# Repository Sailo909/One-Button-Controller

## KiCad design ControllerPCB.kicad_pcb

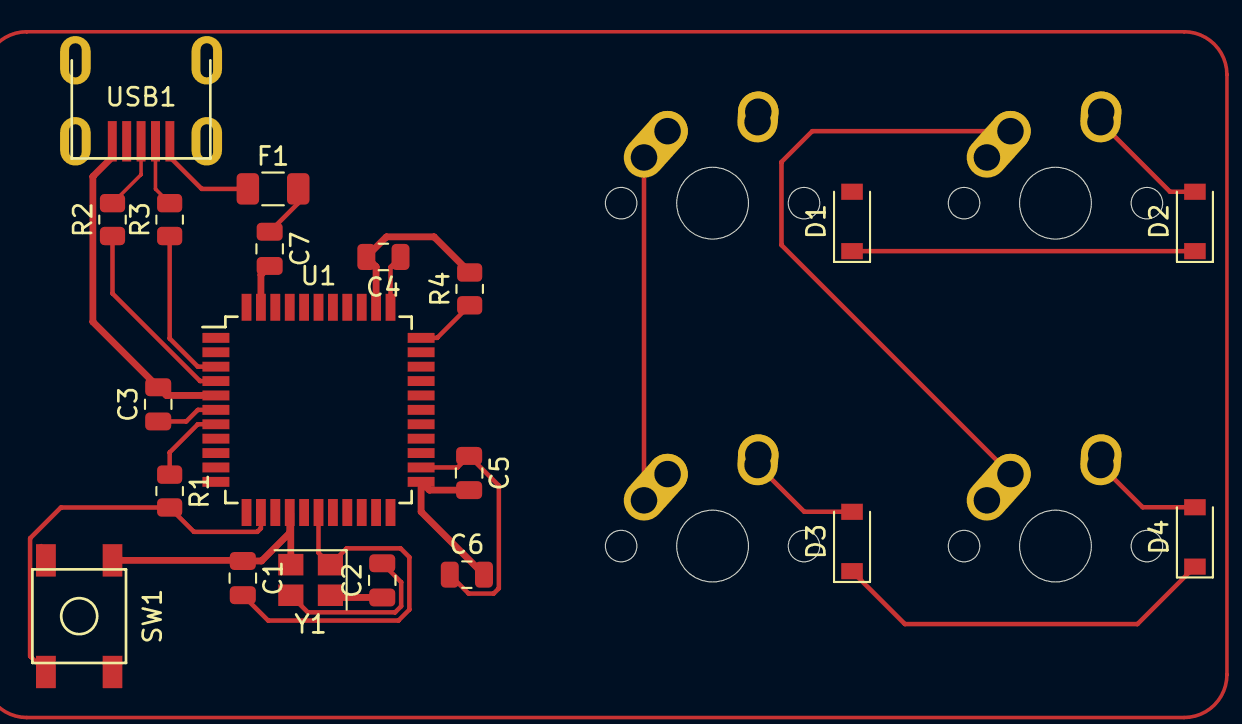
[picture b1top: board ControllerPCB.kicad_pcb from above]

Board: 2 copper layers, 24 parts (0 on the bottom side), 20 nets.

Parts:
C1, C2: 22pF; C_0805_2012Metric
C3: 1uF; C_0805_2012Metric
C4, C5, C6: 0.1uF; C_0805_2012Metric
C7: 10uF; C_0805_2012Metric
D1, D2, D3, D4: SOD-123; D_SOD-123
F1: 500mA; Fuse_1206_3216Metric
MX1, MX2, MX3, MX4: MX-NoLED; MX-1U-NoLED
R1, R4: 10k; R_0805_2012Metric
R2, R3: 22; R_0805_2012Metric
SW1: SW_Push; SKQG-1155865
U1: ATmega32U4-A; TQFP-44_10x10mm_P0.8mm
USB1: Molex-0548190589
Y1: 16MHz; Crystal_SMD_3225-4Pin_3.2x2.5mm

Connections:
+5V: C4.1, C5.1, C6.1, C7.1, F1.2, R1.1, U1.2 (UVCC), U1.7 (VBUS), U1.14 (VCC), U1.24 (AVCC), U1.34 (VCC), U1.44 (AVCC)
/D+: R2.2, USB1.3 (D+)
/D-: R3.2, USB1.4 (D-)
/ROW-0: D1.1 (K), D2.1 (K)
/ROW-1: D3.1 (K), D4.1 (K)
GND: C1.1, C2.1, C3.2, C4.2, C5.2, C6.2, C7.2, R4.2, SW1.1, U1.5 (UGND), U1.15 (GND), U1.23 (GND), U1.35 (GND), U1.43 (GND), USB1.1 (GND), Y1.2, Y1.4
unnamed: C1.2, U1.17 (XTAL1), Y1.1
unnamed: C2.2, U1.16 (XTAL2), Y1.3
unnamed: C3.1, U1.6 (UCAP)
unnamed: D1.2 (A), MX1.2 (ROW)
unnamed: D2.2 (A), MX2.2 (ROW)
unnamed: D3.2 (A), MX3.2 (ROW)
unnamed: D4.2 (A), MX4.2 (ROW)
unnamed: MX1.1 (COL), MX3.1 (COL)
unnamed: MX2.1 (COL), MX4.1 (COL)
unnamed: R1.2, SW1.2, U1.13 (~RESET)
unnamed: R2.1, U1.4 (D+)
unnamed: R3.1, U1.3 (D-)
unnamed: R4.1, U1.33 (~HWB/PE2)
VCC: F1.1, USB1.5 (VBUS)

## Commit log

2022-09-21 Initialize Project
2022-09-21 Add Submodules
2022-09-21 libs added
2022-09-21 PCB started
2022-09-21 PCB updated
2022-09-23 Schematic footprints and labels
